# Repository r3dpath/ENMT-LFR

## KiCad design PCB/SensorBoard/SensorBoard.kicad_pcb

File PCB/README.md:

# --- Group 28 PCB Design Files ---

### PCB's
- MainBoard - The main MCU and motor driver board
- SensorBoard - The primary sensor bar design
- SensorBoardBackup - Alternative seperated sensors just in case

If we could get 5x of each that would be great. For gerbers and drill files see the manufacture subdirectory, or zip file. 
Any questions or issues please get in touch.

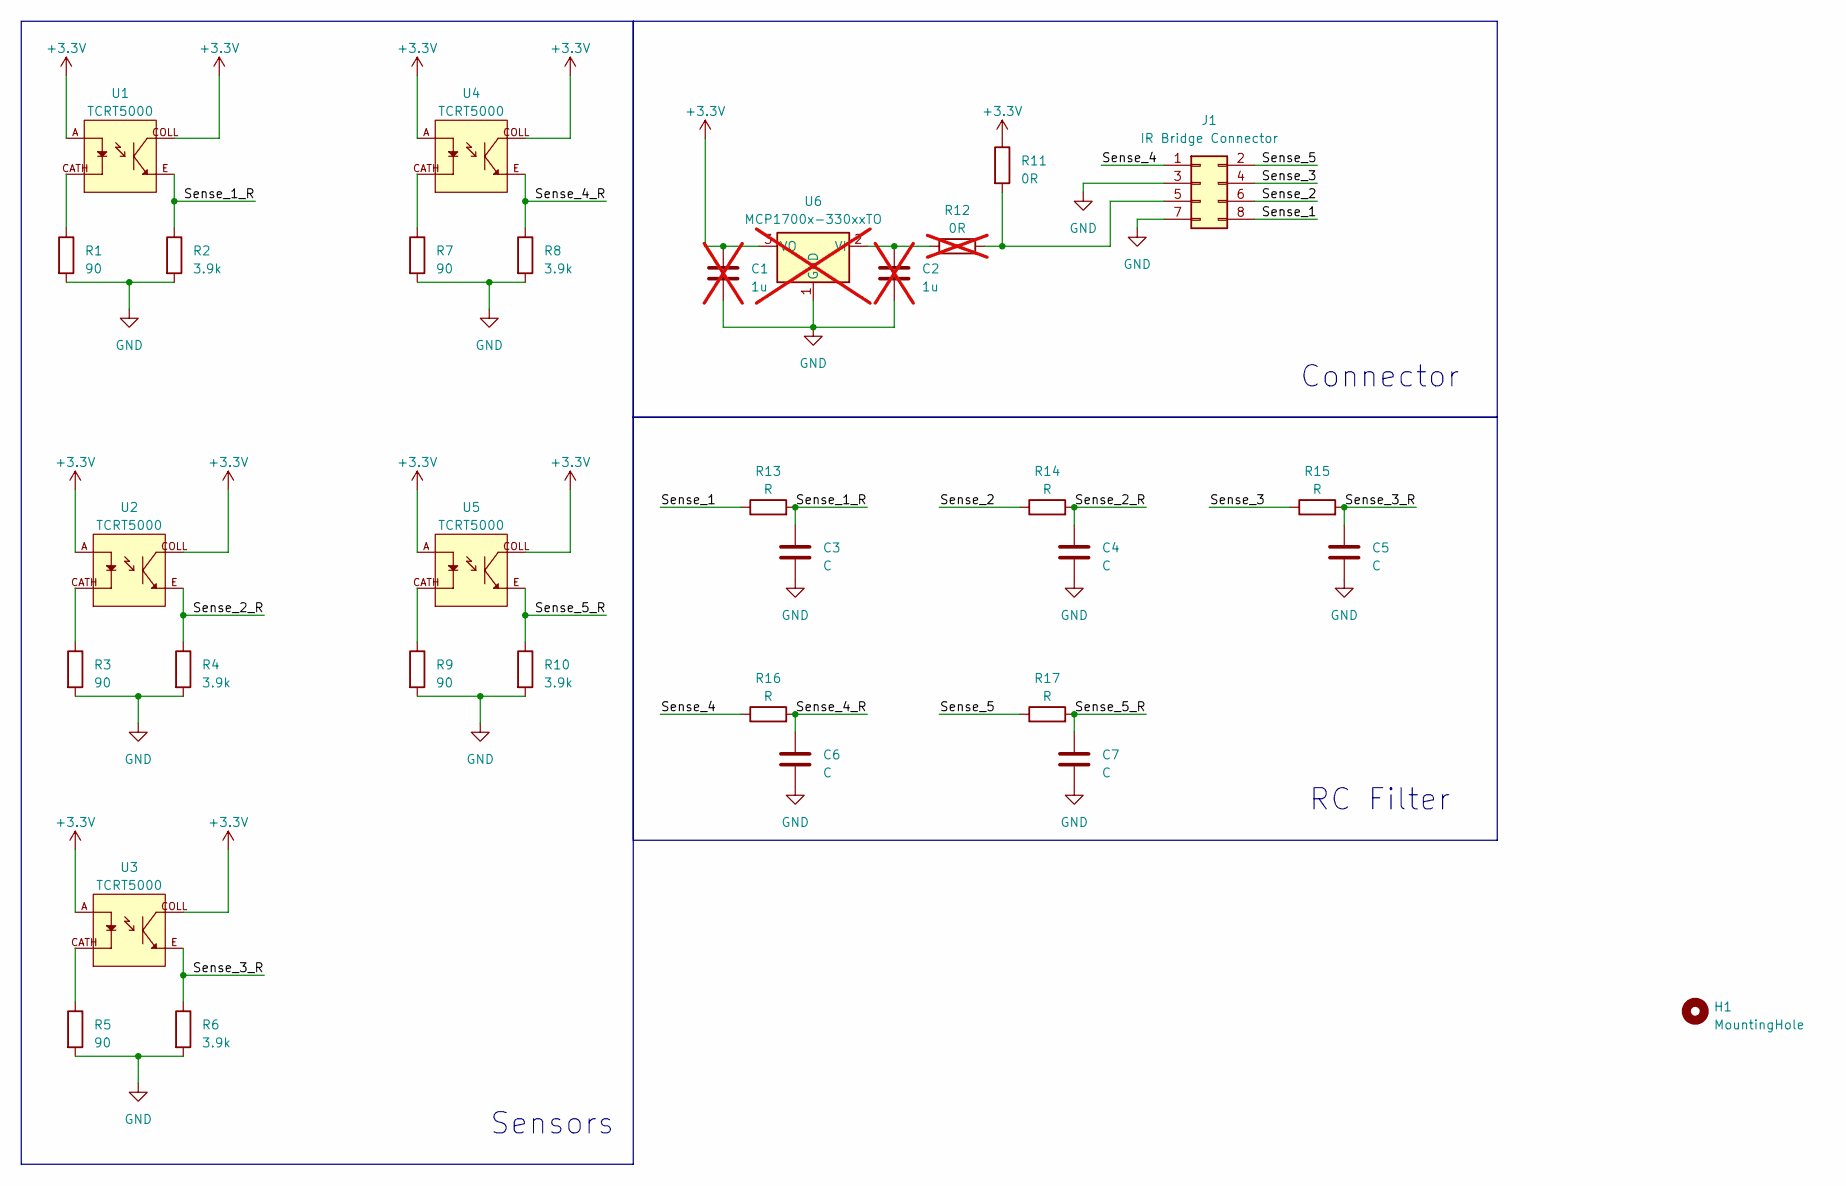
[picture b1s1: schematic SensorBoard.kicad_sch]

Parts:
C1, C2: 1u; C_0603_1608Metric_Pad1.08x0.95mm_HandSolder; not fitted
C3, C4, C5, C6, C7: C; C_1206_3216Metric
H1: MountingHole; MountingHole_2.2mm_M2
J1: IR Bridge Connector; PinHeader_2x04_P2.54mm_Vertical
R1, R3, R5, R7, R9: 90; R_0805_2012Metric
R2, R4, R6, R8, R10: 3.9k; R_0805_2012Metric
R11: 0R; R_0805_2012Metric
R12: 0R; R_0805_2012Metric; not fitted
R13, R14, R15, R16, R17: R; R_0805_2012Metric
U1, U2, U3, U4, U5: TCRT5000; OPTO_TCRT5000; PARTREV 1.7
U6: MCP1700x-330xxTO; TO-92_Inline; not fitted

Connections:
+3.3V: C1.1, R11.1, U1.A, U1.COLL, U2.A, U2.COLL, U3.A, U3.COLL, U4.A, U4.COLL, U5.A, U5.COLL, U6.3 (VO)
/Sense_1: J1.8, R13.1
/Sense_1_R: C3.1, R2.1, R13.2, U1.E
/Sense_2: J1.6, R14.1
/Sense_2_R: C4.1, R4.1, R14.2, U2.E
/Sense_3: J1.4, R15.1
/Sense_3_R: C5.1, R6.1, R15.2, U3.E
/Sense_4: J1.1, R16.1
/Sense_4_R: C6.1, R8.1, R16.2, U4.E
/Sense_5: J1.2, R17.1
/Sense_5_R: C7.1, R10.1, R17.2, U5.E
GND: C1.2, C2.2, C3.2, C4.2, C5.2, C6.2, C7.2, J1.3, J1.7, R1.2, R2.2, R3.2, R4.2, R5.2, R6.2, R7.2, R8.2, R9.2, R10.2, U6.1 (GND)
unnamed: J1.5, R11.2, R12.2
unnamed: R1.1, U1.CATH
unnamed: R3.1, U2.CATH
unnamed: R5.1, U3.CATH
unnamed: R7.1, U4.CATH
unnamed: R9.1, U5.CATH
unnamed: C2.1, R12.1, U6.2 (VI)

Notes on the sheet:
Sensors
RC Filter
Connector

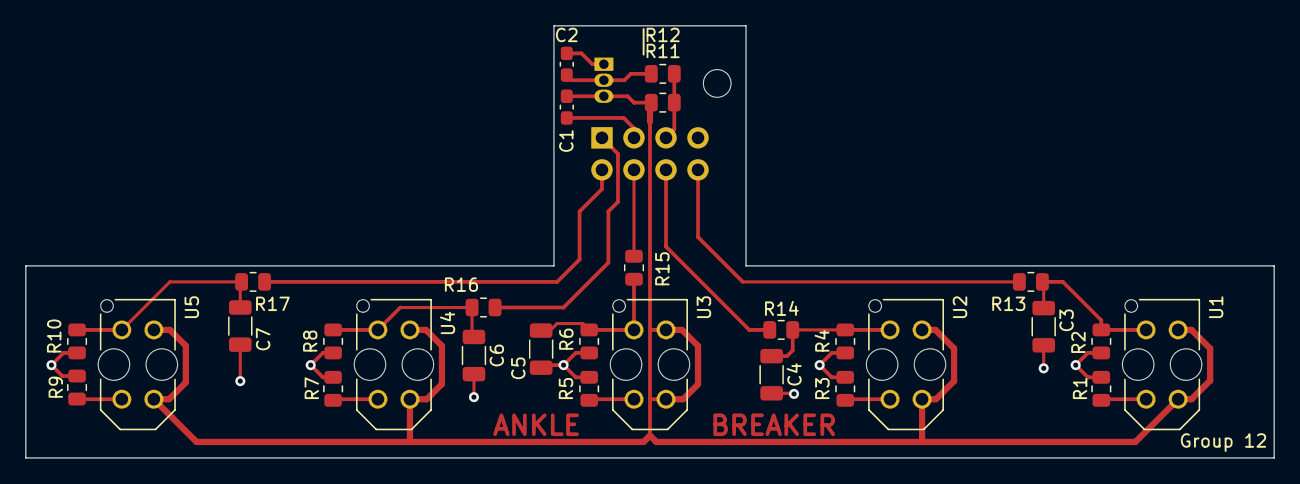
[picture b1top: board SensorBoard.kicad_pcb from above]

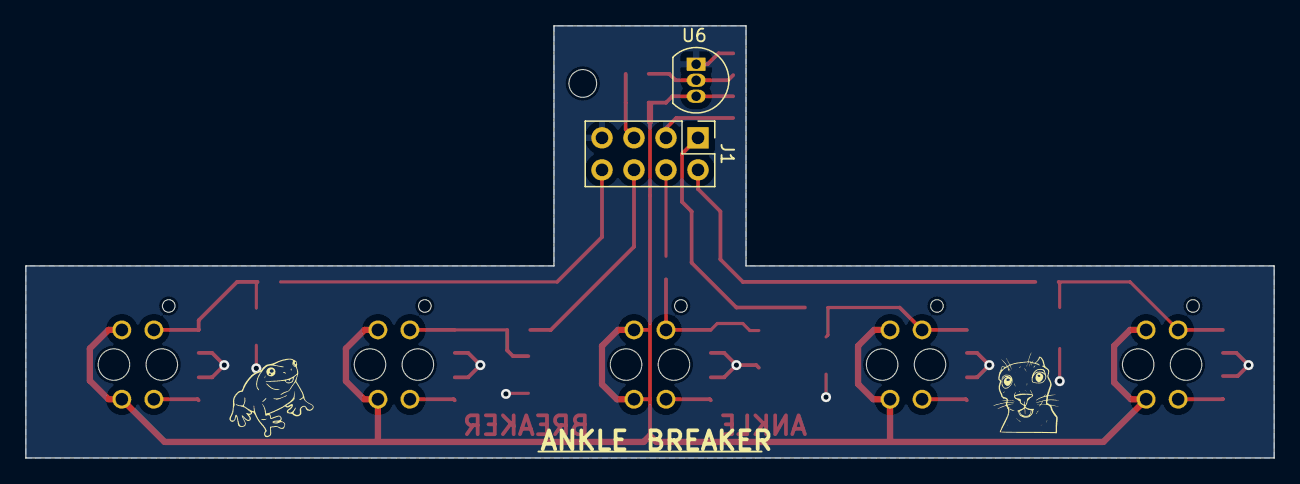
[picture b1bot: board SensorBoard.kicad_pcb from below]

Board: 2 copper layers, 99.1 x 34.3 mm, 32 parts (2 on the bottom side), 19 nets.

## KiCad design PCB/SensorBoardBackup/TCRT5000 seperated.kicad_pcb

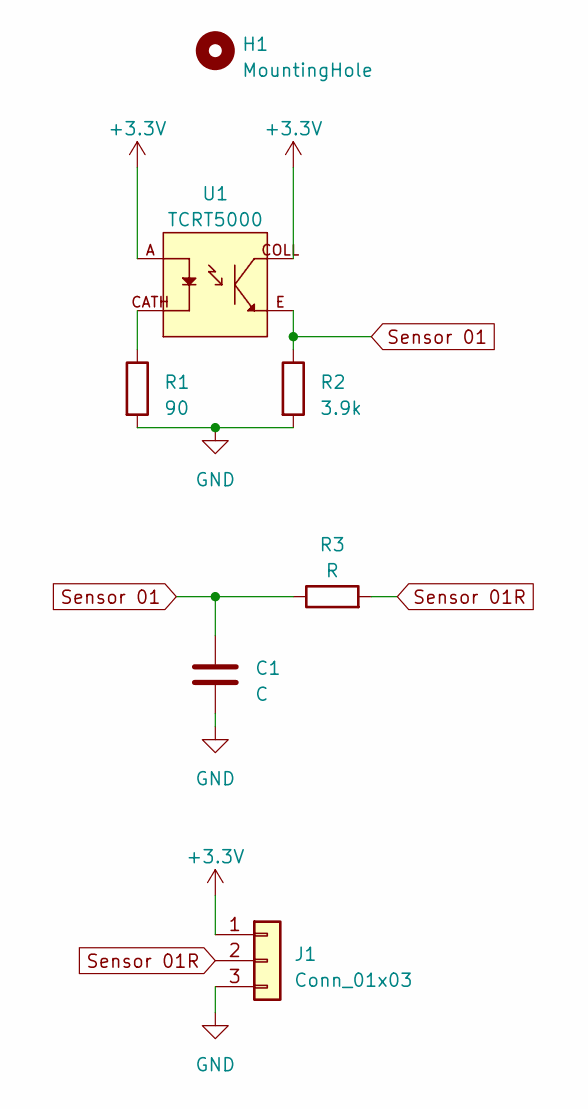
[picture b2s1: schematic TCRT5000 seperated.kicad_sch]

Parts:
C1: C; C_1206_3216Metric
H1: MountingHole; MountingHole_3mm
J1: Conn_01x03; PinHeader_1x03_P2.54mm_Vertical
R1: 90; R_0805_2012Metric
R2: 3.9k; R_0805_2012Metric
R3: R; R_0805_2012Metric
U1: TCRT5000; OPTO_TCRT5000; PARTREV 1.7

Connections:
+3.3V: J1.1, U1.A, U1.COLL
GND: C1.2, J1.3, R1.2, R2.2
unnamed: R1.1, U1.CATH
Sensor 01: C1.1, R2.1, R3.1, U1.E
Sensor 01R: J1.2, R3.2

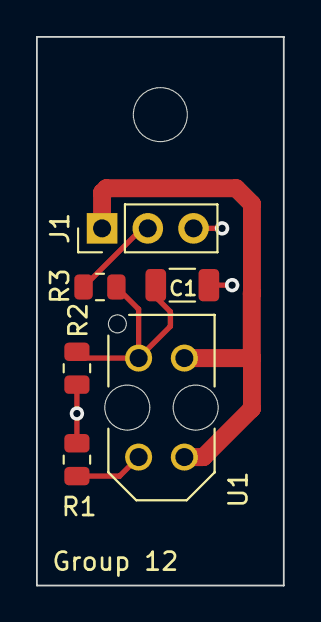
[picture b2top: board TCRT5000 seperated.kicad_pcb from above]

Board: 2 copper layers, 13.7 x 30.5 mm, 7 parts (0 on the bottom side), 5 nets.

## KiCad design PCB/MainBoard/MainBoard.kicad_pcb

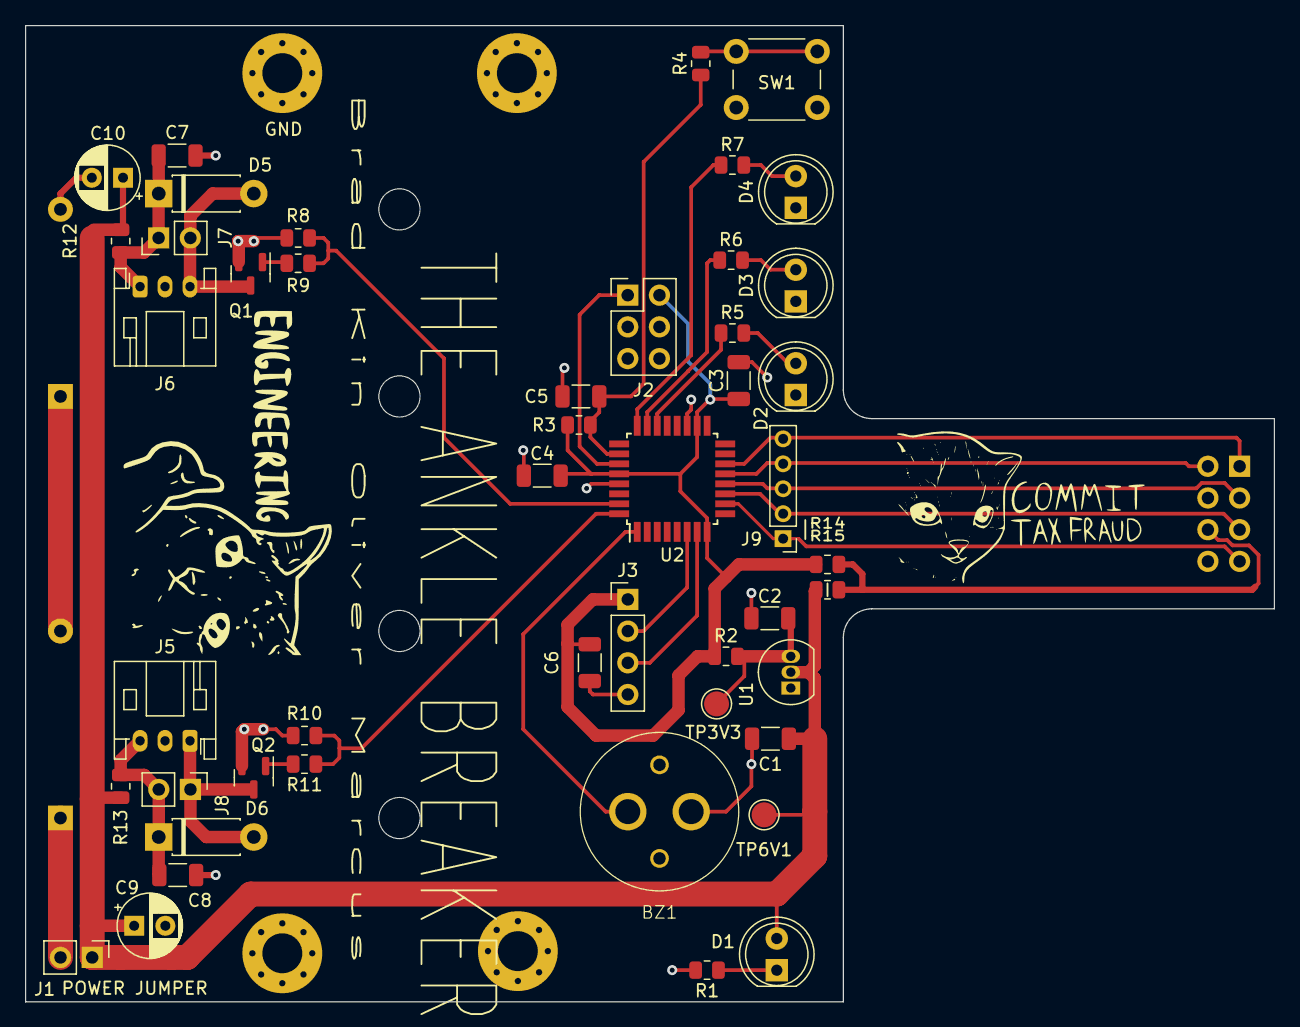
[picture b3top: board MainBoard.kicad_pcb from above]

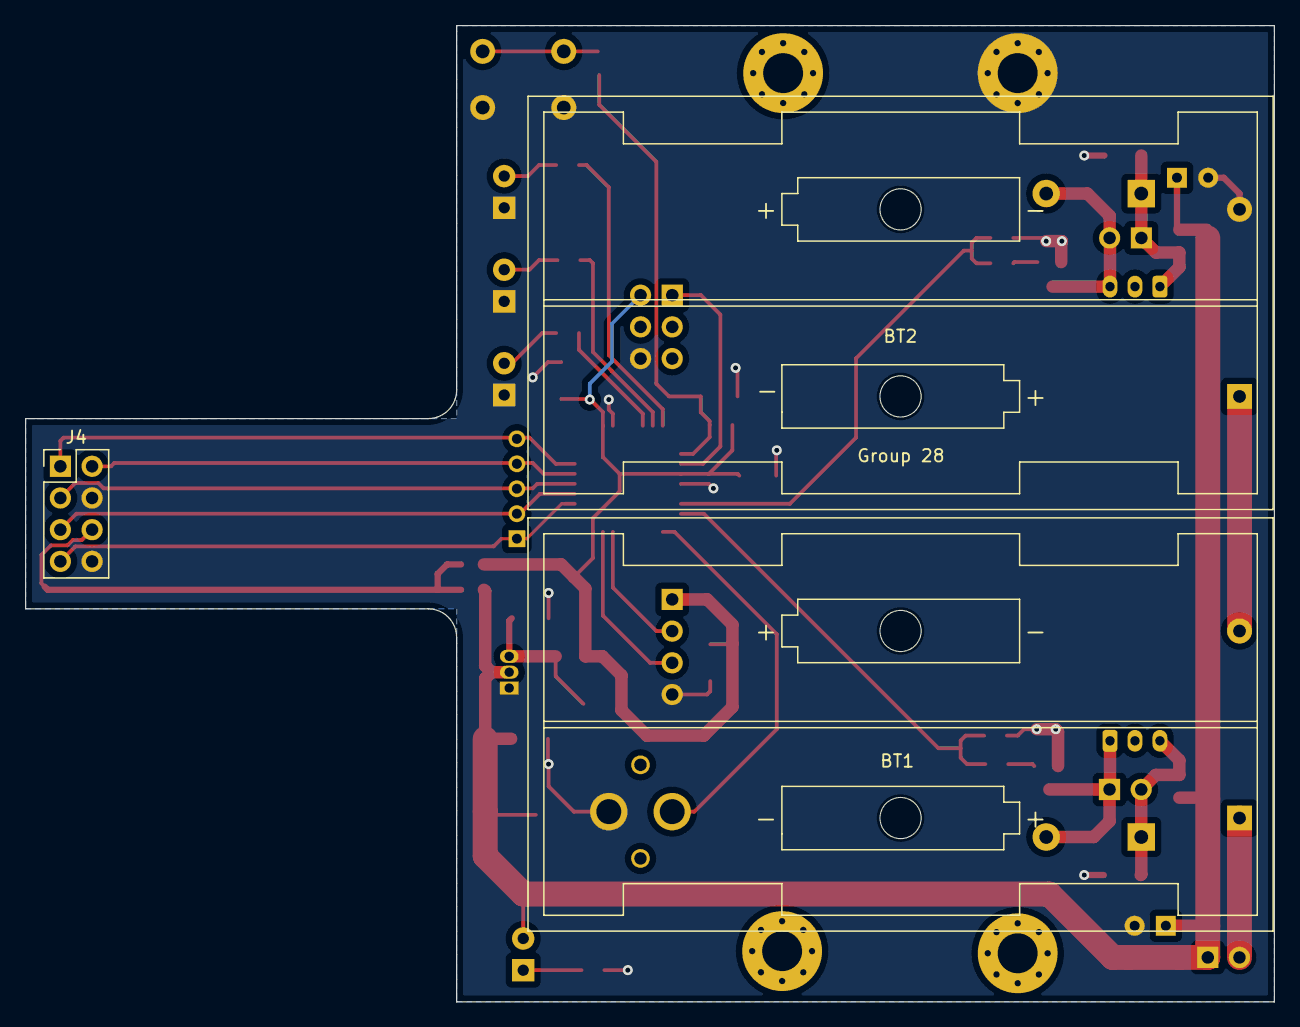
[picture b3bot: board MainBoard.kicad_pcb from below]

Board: 2 copper layers, 100.1 x 78.2 mm, 54 parts (3 on the bottom side), 33 nets.

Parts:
BT1, BT2: 3V; BatteryHolder_Keystone_2462_2xAA
BZ1: Buzzer; PKM13EPYH4000
C1, C2: 1u; C_1206_3216Metric
C3, C4, C5, C6: 100n; C_1206_3216Metric
C7, C8: 10u; C_1206_3216Metric
C9, C10: C; CP_Radial_D5.0mm_P2.50mm
D1, D2, D3, D4: LED; LED_D5.0mm
D5, D6: SB130; D_DO-41_SOD81_P7.62mm_Horizontal
H1, H2, H3, H4: MountingHole; MountingHole_3.2mm_M3_Pad_Via
J1: Switch; PinHeader_1x02_P2.54mm_Vertical
J2: Prog Connector; PinHeader_2x03_P2.54mm_Vertical
J3: UART; PinHeader_1x04_P2.54mm_Vertical
J4: IR Connector; PinHeader_2x04_P2.54mm_Vertical
J5: R Motor; JST_PH_S3B-PH-K_1x03_P2.00mm_Horizontal
J6: L_Motor; JST_PH_S3B-PH-K_1x03_P2.00mm_Horizontal
J7: L_Motor_Backup; PinHeader_1x02_P2.54mm_Vertical
J8: R_Motor_Backup; PinHeader_1x02_P2.54mm_Vertical
J9: Backup connector bit; PinHeader_1x05_P2.00mm_Vertical
Q1, Q2: BSR802; SOT-23
R1, R5, R6, R7: 470R; R_0805_2012Metric
R2, R12, R13, R14, R15: 0R; R_0805_2012Metric
R3: 4.7k; R_0805_2012Metric
R4: 330; R_0805_2012Metric
R8, R10: 10000; R_0805_2012Metric
R9, R11: 100; R_0805_2012Metric
SW1: RESET_SW; SW_PUSH_6mm
TP3V3, TP6V1: TestPoint; TestPoint_Pad_D2.0mm
U1: MCP1700-3302E/TO; TO-92_Inline
U2: ATmega4808-A; TQFP-32_7x7mm_P0.8mm

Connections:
+3V3: C3.1, C4.1, C6.1, J2.2, J3.1, R2.1, R3.1, R14.1, U2.8 (PC2), U2.18 (AVDD), U2.28 (VDD)
+6V: C1.1, C9.1, C10.1, D1.2 (A), J1.1, R12.1, R13.1, R15.1, TP6V1.1, U1.2 (VI)
/BUZZER: BZ1.1 (-), U2.1 (PA3)
/IR_1: J4.7, J9.1, U2.10 (PD0)
/IR_2: J4.5, J9.2, U2.11 (PD1)
/IR_3: J4.3, J9.3, U2.12 (PD2)
/IR_4: J4.2, J9.4, U2.13 (PD3)
/IR_5: J4.1, J9.5, U2.14 (PD4)
/LED_1: R5.1, U2.22 (PF2)
/LED_2: R6.1, U2.23 (PF3)
/LED_3: R7.1, U2.24 (PF4)
/L_MOTOR_PWM: R8.1, R9.1, U2.31 (PA1)
/RESET: C5.1, R3.2, R4.1, U2.26 (PF6/~RESET)
/R_MOTOR_PWM: R10.1, R11.1, U2.32 (PA2)
/RxD: J3.3, U2.7 (PC1)
/TxD: J3.2, U2.6 (PC0)
/UPDI_DATA: J2.1, U2.27 (UPDI)
GND: BT2.2 (-), BZ1.2 (+), C1.2, C2.2, C3.2, C4.2, C5.2, C6.2, C7.2, C8.2, C9.2, C10.2, D2.1 (K), D3.1 (K), D4.1 (K), H1.1, J2.6, J3.4, J4.4, J4.8, Q1.2 (S), Q2.2 (S), R1.2, R8.2, R10.2, SW1.2 (B), U1.1 (GND), U2.19 (GND), U2.29 (GND)
unnamed: BT1.1 (+), J1.2
unnamed: BT1.2 (-), BT2.1 (+)
unnamed: D1.1 (K), R1.1
unnamed: D2.2 (A), R5.2
unnamed: D3.2 (A), R6.2
unnamed: D4.2 (A), R7.2
unnamed: D5.2 (A), J6.3, J7.2, Q1.3 (D)
unnamed: C7.1, D5.1 (K), J6.1, J7.1, R12.2
unnamed: D6.2 (A), J5.1, J8.1, Q2.3 (D)
unnamed: C8.1, D6.1 (K), J5.3, J8.2, R13.2
unnamed: J4.6, R14.2, R15.2
unnamed: Q1.1 (G), R9.2
unnamed: Q2.1 (G), R11.2
unnamed: R4.2, SW1.1 (A)
unnamed: C2.1, R2.2, TP3V3.1, U1.3 (VO)

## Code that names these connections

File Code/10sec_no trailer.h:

#ifndef LFR_H
#define LFR_H

#include <Arduino.h>

#define L_MOTOR PIN_PA1
#define R_MOTOR PIN_PA2
#define BUZZER_PIN PIN_PA3
#define LED_1 PIN_PF2
#define LED_2 PIN_PF3 
#define LED_3 PIN_PF4

#define IR_1 PIN_PD0 
#define IR_2 PIN_PD1 
#define IR_3 PIN_PD2 
#define IR_4 PIN_PD3 
#define IR_5 PIN_PD4

#define SENSOR_MIN_THRESHOLD 170
#define SENSOR_SIDE_THRESHOLD 180

// #define SENSOR_MIN_THRESHOLD 50
// #define SENSOR_SIDE_THRESHOLD 0

#define Kp 0.7  // Proportional constant - You might need to tune this
#define Ki 0  // Integral constant - Start with 0 and tune later if needed
#define Kd 5  // Derivative constant - You might need to tune this

#define BaseSpeed 65
#define MaxSpeed 70
#define BoostSpeed 0
#define LBias 1.1

typedef enum {
    LEFTMOTOR,
    RIGHTMOTOR
} motor_t;

void setup_PWM(void);
void motorUpdate(void);
void setMotor(uint8_t, uint8_t);
void sensorPrint(uint8_t*);
uint8_t sensorParse(uint8_t*);


#endif //LFR_H

//base = 40, Kp = 0.8, Ki = 0, Kd = 0.02
//

//---
// 11 sec w rubber bands

// #define baseSpeed 75
// #define maxSpeed 75

// #define Kp 1.2  // Proportional constant - You might need to tune this
// #define Ki 0  // Integral constant - Start with 0 and tune later if needed
// #define Kd 1  // Derivative constant - You might need to tune this

//w base + 30, max + 25
//---

/*
Solid 12s run with wire slowdown
#define Kp 1.2  // Proportional constant - You might need to tune this
#define Ki 0.001  // Integral constant - Start with 0 and tune later if needed
#define Kd 10  // Derivative constant - You might need to tune this

#define baseSpeed 60
#define maxSpeed 65
#define boostSpeed 0
*/

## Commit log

2023-09-17 Initial
2023-09-17 Added cad sketch
2023-09-18 Added MCU supporting components
2023-09-18 Added CAD Stuff
2023-09-18 More cad
2023-09-19 Added CAD with gears
2023-09-19 Removed .DS_Store
2023-09-19 Added sensor board
2023-09-20 Add files via upload
    version 2
2023-09-20 Progress on Main Board
2023-09-20 More main
2023-09-20 Changed Sensor Board
2023-09-20 Routed main board
2023-09-21 Edits to both boards
2023-09-21 Cleaned up repo
2023-09-21 Added 3d model
2023-09-21 Cleaned up mainboard
2023-09-21 Cleaned up sensor board
2023-09-22 Clean up seperate sensor
2023-09-22 Version that was submitted
2023-09-22 Version that was resubmitted
2023-09-26 Some initial platformio setup
2023-10-06 Some more initial programming for atmelice
2023-10-09 For print wheels
2023-10-09 Wheel Mounts
2023-10-10 wheel mount
2023-10-10 Random
2023-10-11 Coding stuff
2023-10-11 Added mods to platformio
2023-10-11 Scuffed position sensing
2023-10-13 Semi-functonal arduino
2023-10-13 updated Arduino
2023-10-13 Motors working
2023-10-13 Not working
2023-10-13 updated line following program
2023-10-13 Platform part working
2023-10-14 modified parts and assembly
2023-10-14 Cleanup
2023-10-17 Code changes and stuff
2023-10-17 Merged codebase
2023-10-17 Promising
2023-10-18 Spaer with nut
2023-10-19 Part working
2023-10-20 Final code after comp
2023-10-22 Cleaned up some CAD
